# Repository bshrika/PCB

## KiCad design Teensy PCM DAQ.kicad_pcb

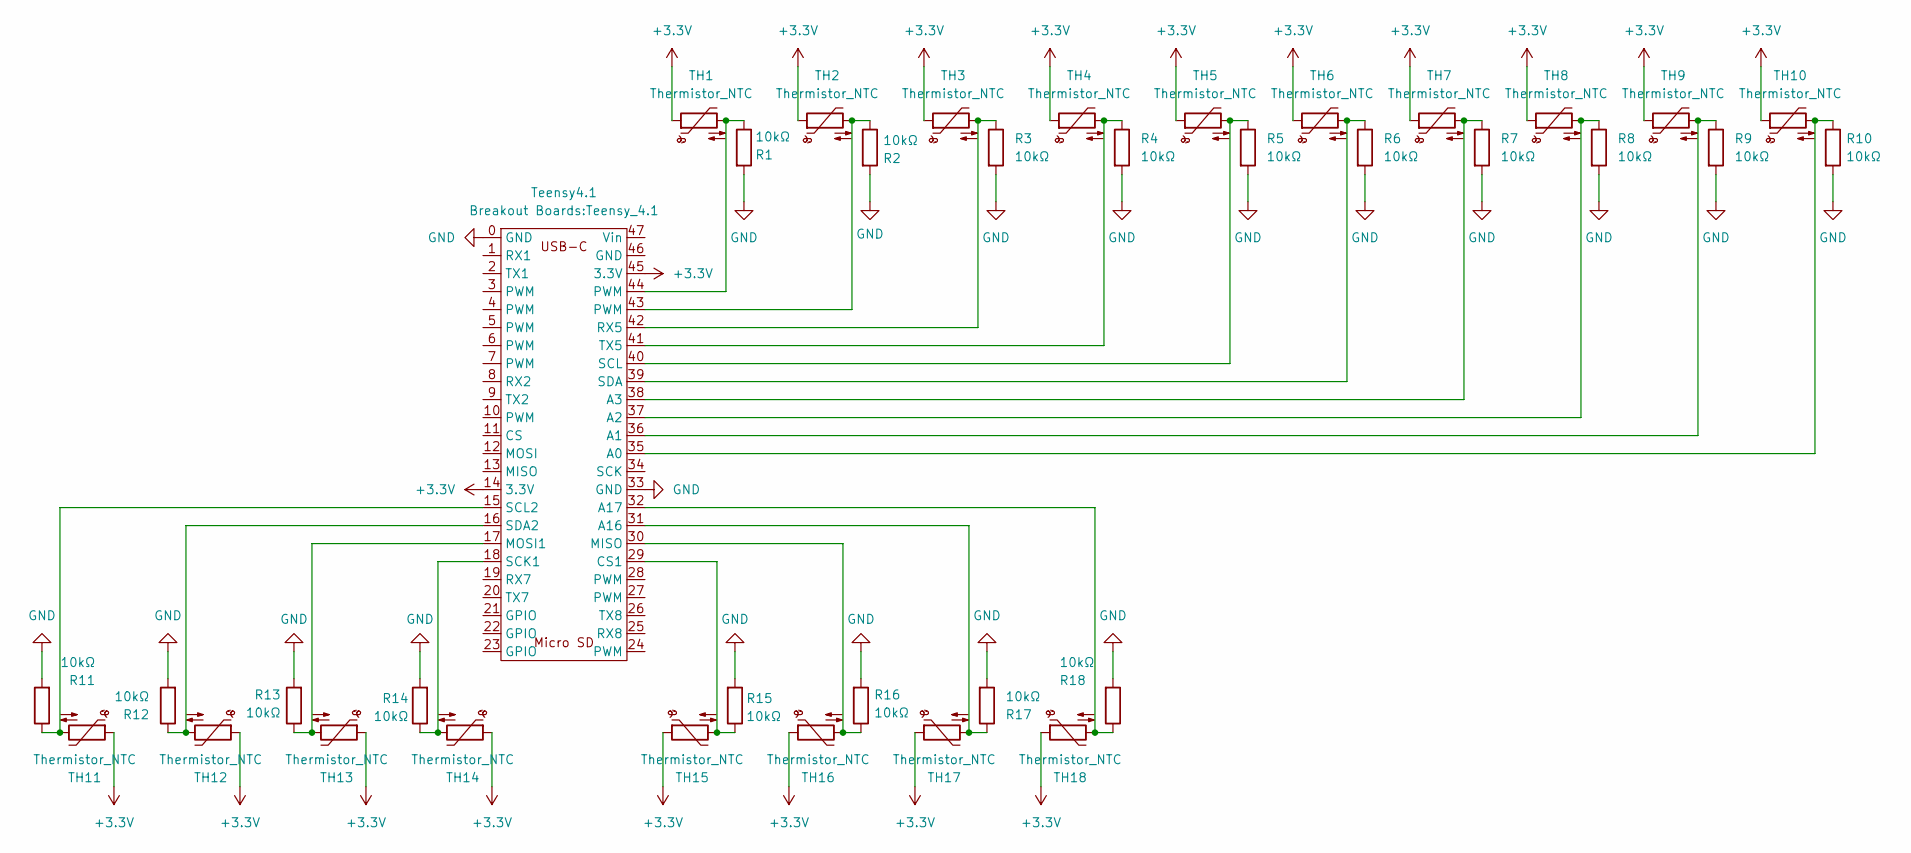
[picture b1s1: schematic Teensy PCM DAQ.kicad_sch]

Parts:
R1, R2, R3, R4, R5, R6, R7, R8, R9, R10, R11, R12, R13, R14, R15, R16, R17, R18: 10kΩ; R_Axial_DIN0204_L3.6mm_D1.6mm_P7.62mm_Horizontal
TH1, TH2, TH3, TH4, TH5, TH6, TH7, TH8, TH9, TH10, TH11, TH12, TH13, TH14, TH15, TH16, TH17, TH18: Thermistor_NTC; JST_EH_B2B-EH-A_1x02_P2.50mm_Vertical
Teensy4.1: Teensy_4.1

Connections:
+3.3V: TH1.1, TH2.1, TH3.1, TH4.1, TH5.1, TH6.1, TH7.1, TH8.1, TH9.1, TH10.1, TH11.1, TH12.1, TH13.1, TH14.1, TH15.1, TH16.1, TH17.1, TH18.1, Teensy4.1.14 (3.3V), Teensy4.1.45 (3.3V)
GND: R1.2, R2.2, R3.2, R4.2, R5.2, R6.2, R7.2, R8.2, R9.2, R10.2, R11.2, R12.2, R13.2, R14.2, R15.2, R16.2, R17.2, R18.2, Teensy4.1.0 (GND), Teensy4.1.33 (GND)
unnamed: R1.1, TH1.2, Teensy4.1.44 (PWM)
unnamed: R2.1, TH2.2, Teensy4.1.43 (PWM)
unnamed: R16.1, TH16.2, Teensy4.1.30 (MISO)
unnamed: R10.1, TH10.2, Teensy4.1.35 (A0)
unnamed: R9.1, TH9.2, Teensy4.1.36 (A1)
unnamed: R8.1, TH8.2, Teensy4.1.37 (A2)
unnamed: R7.1, TH7.2, Teensy4.1.38 (A3)
unnamed: R17.1, TH17.2, Teensy4.1.31 (A16)
unnamed: R18.1, TH18.2, Teensy4.1.32 (A17)
unnamed: R15.1, TH15.2, Teensy4.1.29 (CS1)
unnamed: R13.1, TH13.2, Teensy4.1.17 (MOSI1)
unnamed: R3.1, TH3.2, Teensy4.1.42 (RX5)
unnamed: R14.1, TH14.2, Teensy4.1.18 (SCK1)
unnamed: R11.1, TH11.2, Teensy4.1.15 (SCL2)
unnamed: R5.1, TH5.2, Teensy4.1.40 (SCL)
unnamed: R12.1, TH12.2, Teensy4.1.16 (SDA2)
unnamed: R6.1, TH6.2, Teensy4.1.39 (SDA)
unnamed: R4.1, TH4.2, Teensy4.1.41 (TX5)

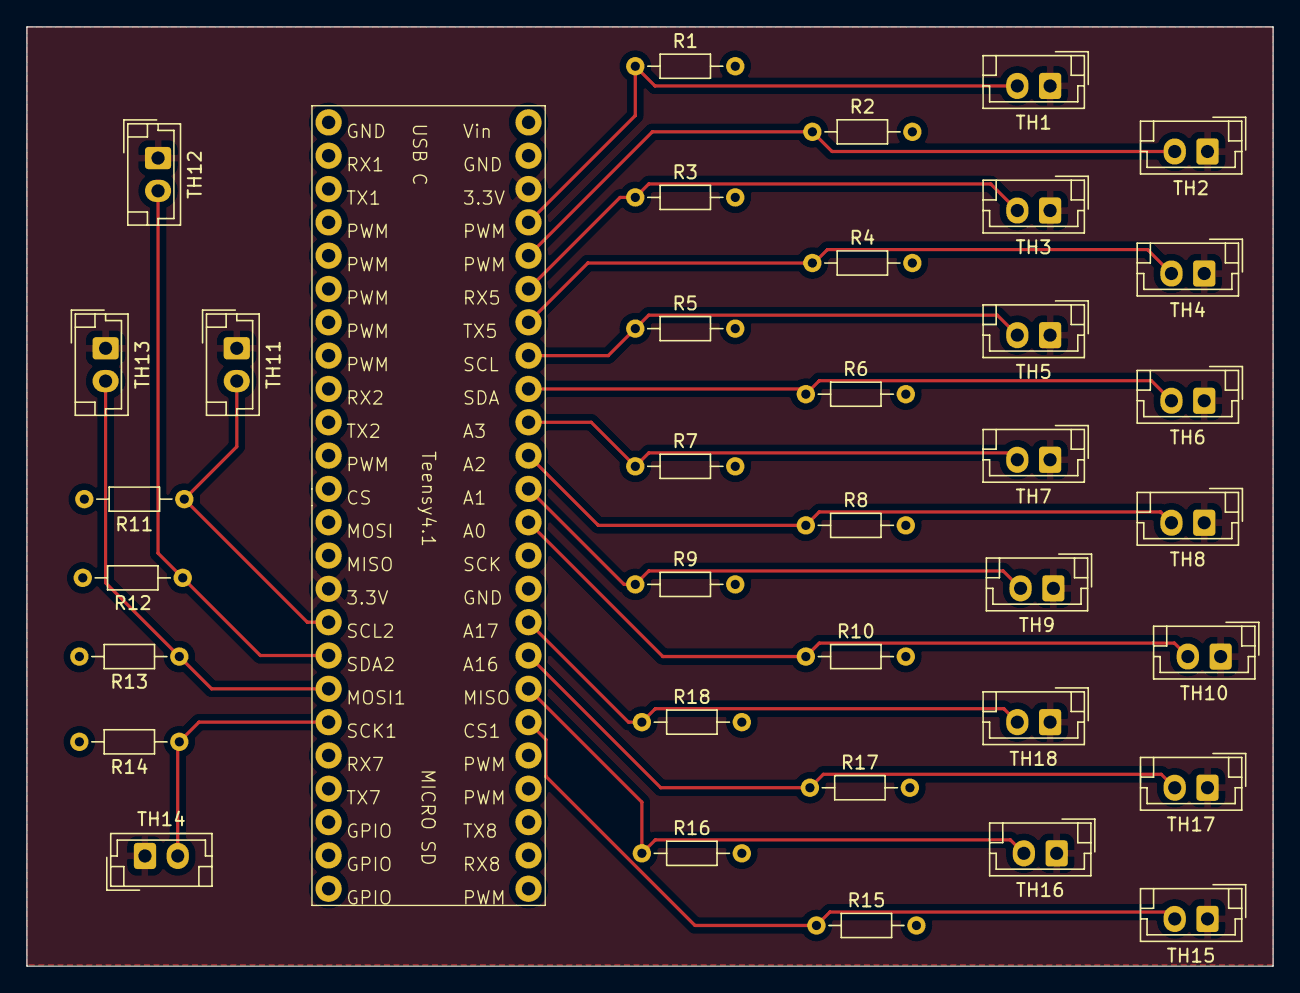
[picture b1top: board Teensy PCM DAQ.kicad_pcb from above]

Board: 2 copper layers, 95.0 x 71.6 mm, 37 parts (0 on the bottom side), 20 nets.

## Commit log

2025-04-07 fuvl mr
